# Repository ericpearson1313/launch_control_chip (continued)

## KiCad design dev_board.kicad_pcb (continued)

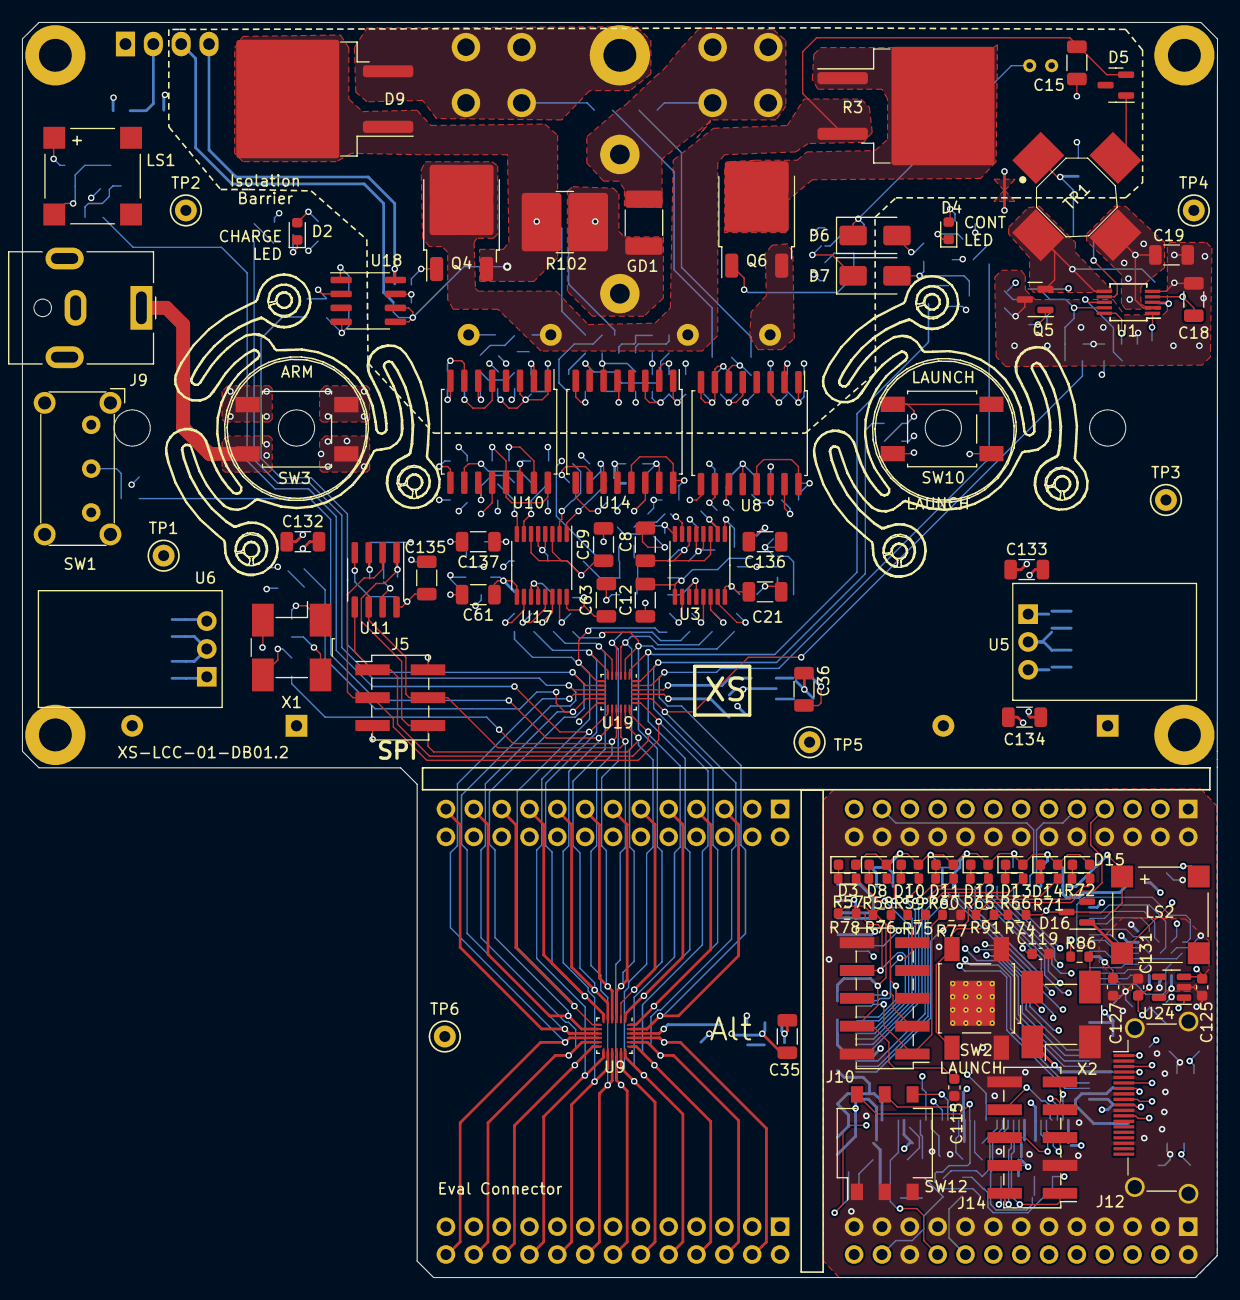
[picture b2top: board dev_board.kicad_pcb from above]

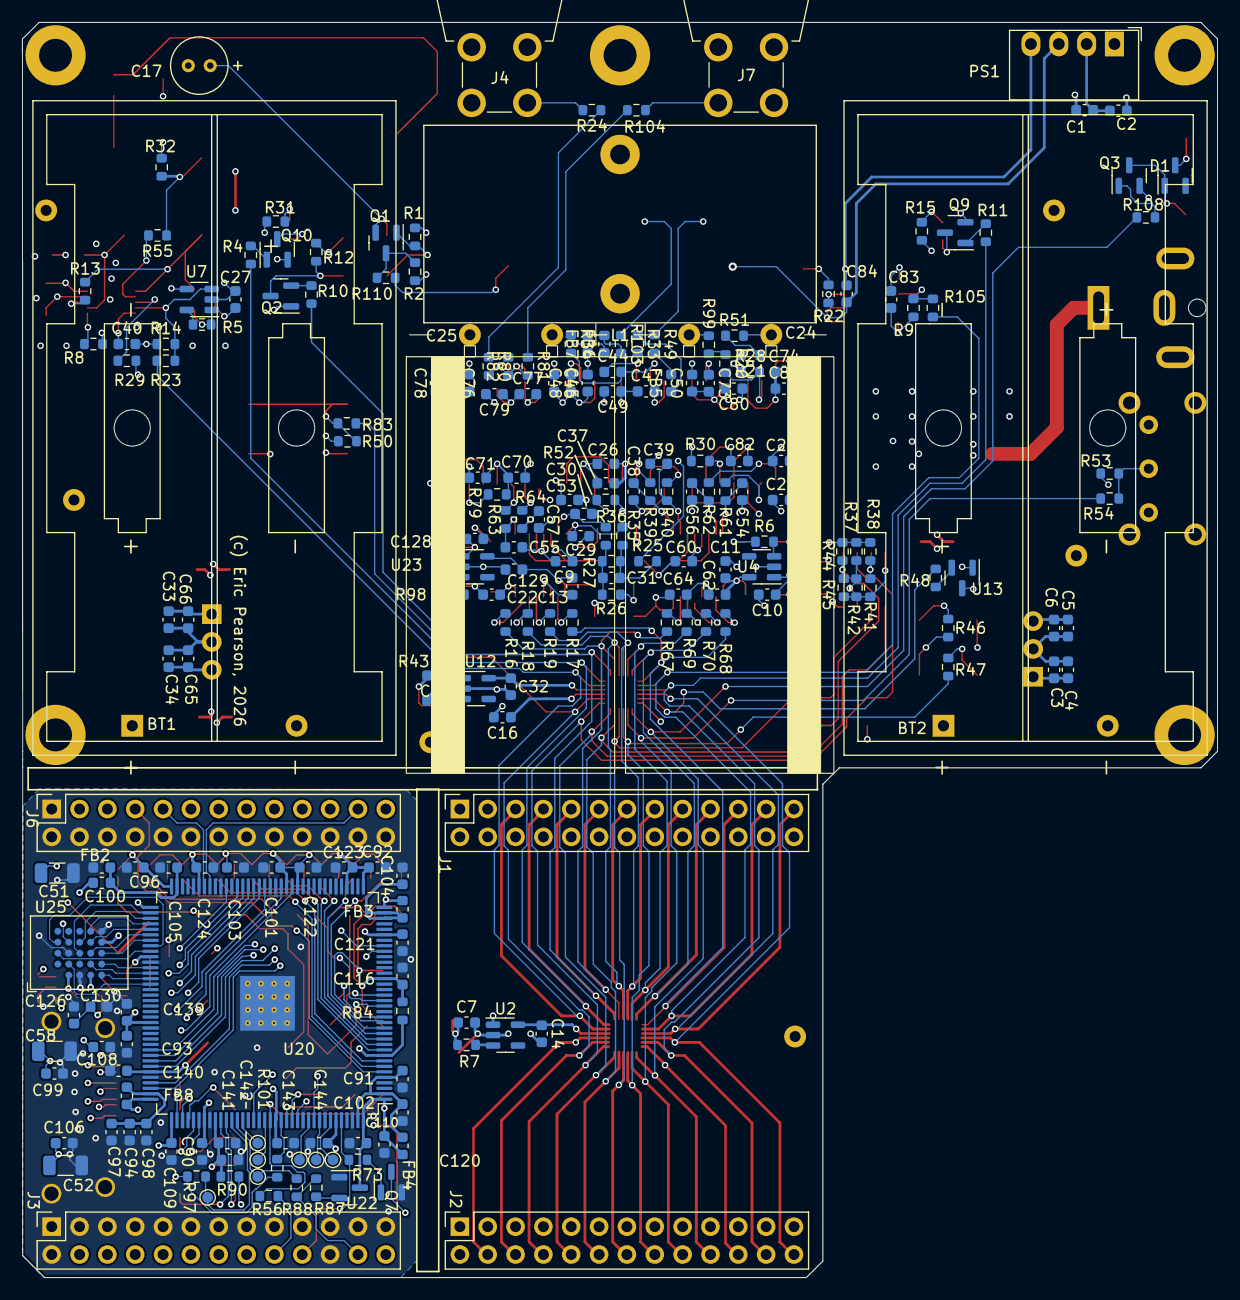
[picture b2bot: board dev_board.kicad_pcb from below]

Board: 6 copper layers, 109.0 x 114.5 mm, 323 parts (224 on the bottom side), 195 nets.

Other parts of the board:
R3: 3K3 25W; TO-263-2_TabPin1

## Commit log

2025-08-28 Arch draft slides
2025-09-12 slide 3
2025-09-12 Update README.md slide 3
2025-09-13 slide 4
2025-09-13 Update README.md with package drawing
2025-09-16 preliminary pinout and signal description
2025-09-16 add pinout snapshot
2025-09-19 move pinout slide
2025-10-02 Add Eval board slide picture, value, features
2025-10-02 Update README.md with evaluation board slide
2025-10-06 update eval board features and photo
2025-10-18 Add EB example applications
2025-10-18 add eval board circuit examples
2025-10-18 Add minimum viable circuit for EB
2025-10-21 5 wire launch cable
2026-02-05 add pdf draft of architecture slides
2026-02-05 LCC Dev Board v0.1 KiCad project, schematic and pcb
2026-02-05 Added Dev Board development notes
2026-02-09 Closer to tapeout, Digikey BOM added
2026-02-10 Update README with datasheet link
    Added a link to the datasheet for the launch chip.
2026-02-10 Added PCB links
    Updated sections for clarity and added links to KiCAD files.
2026-02-21 prelim dev board
2026-02-21 dev board slide README
2026-02-23 Tapeout v01.2
2026-02-23 Updated dev board slide to match v1.2 pcb tapeout
2026-05-10 LCC-XB experimental engineering 24 pin DIP module draft v0.1
2026-05-10 Add datasheet page for LCC engineering experimental PCB (24pin DIP module)
2026-05-12 change back to dual ADCs (with internal refs) for now. Leave the low cost ADCs to the future
2026-05-24 MVP enclosure parts
2026-05-24 Update README with prototype launch controller details
    Added information about extra prototype devices for sale.
2026-05-26 Add psb tapeout gerbers
2026-05-26 Add dev board PCB ECO notes text file.
2026-05-30 Added flyback routing feedback.
